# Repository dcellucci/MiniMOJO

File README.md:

# MiniMOJO

Documentation, hardware, and software related to MiniMOJO, a robot capable of traversing a digital cellular solids lattice.

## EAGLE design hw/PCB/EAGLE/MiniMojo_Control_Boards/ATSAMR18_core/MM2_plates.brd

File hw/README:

# Hardware Notes

## MOJO Boards Rev 3

That's the one with the battery backpack.

### TeuxDeux

 1. Add solder jumper to disconnect power for I2C cable
 2. Move backpack switch to somewhere reachable
 	2a. backpack switch should turn IC on/off, IC should turn motors on/off
 3. Move servo connector up

### Notes

Pinout for ATSAM

    6 Pin | 10 Pin SAM 

    1 > 2
    2 > 1
    3 > 4
    4 > DNC 
    5 > 0
    6 > 5

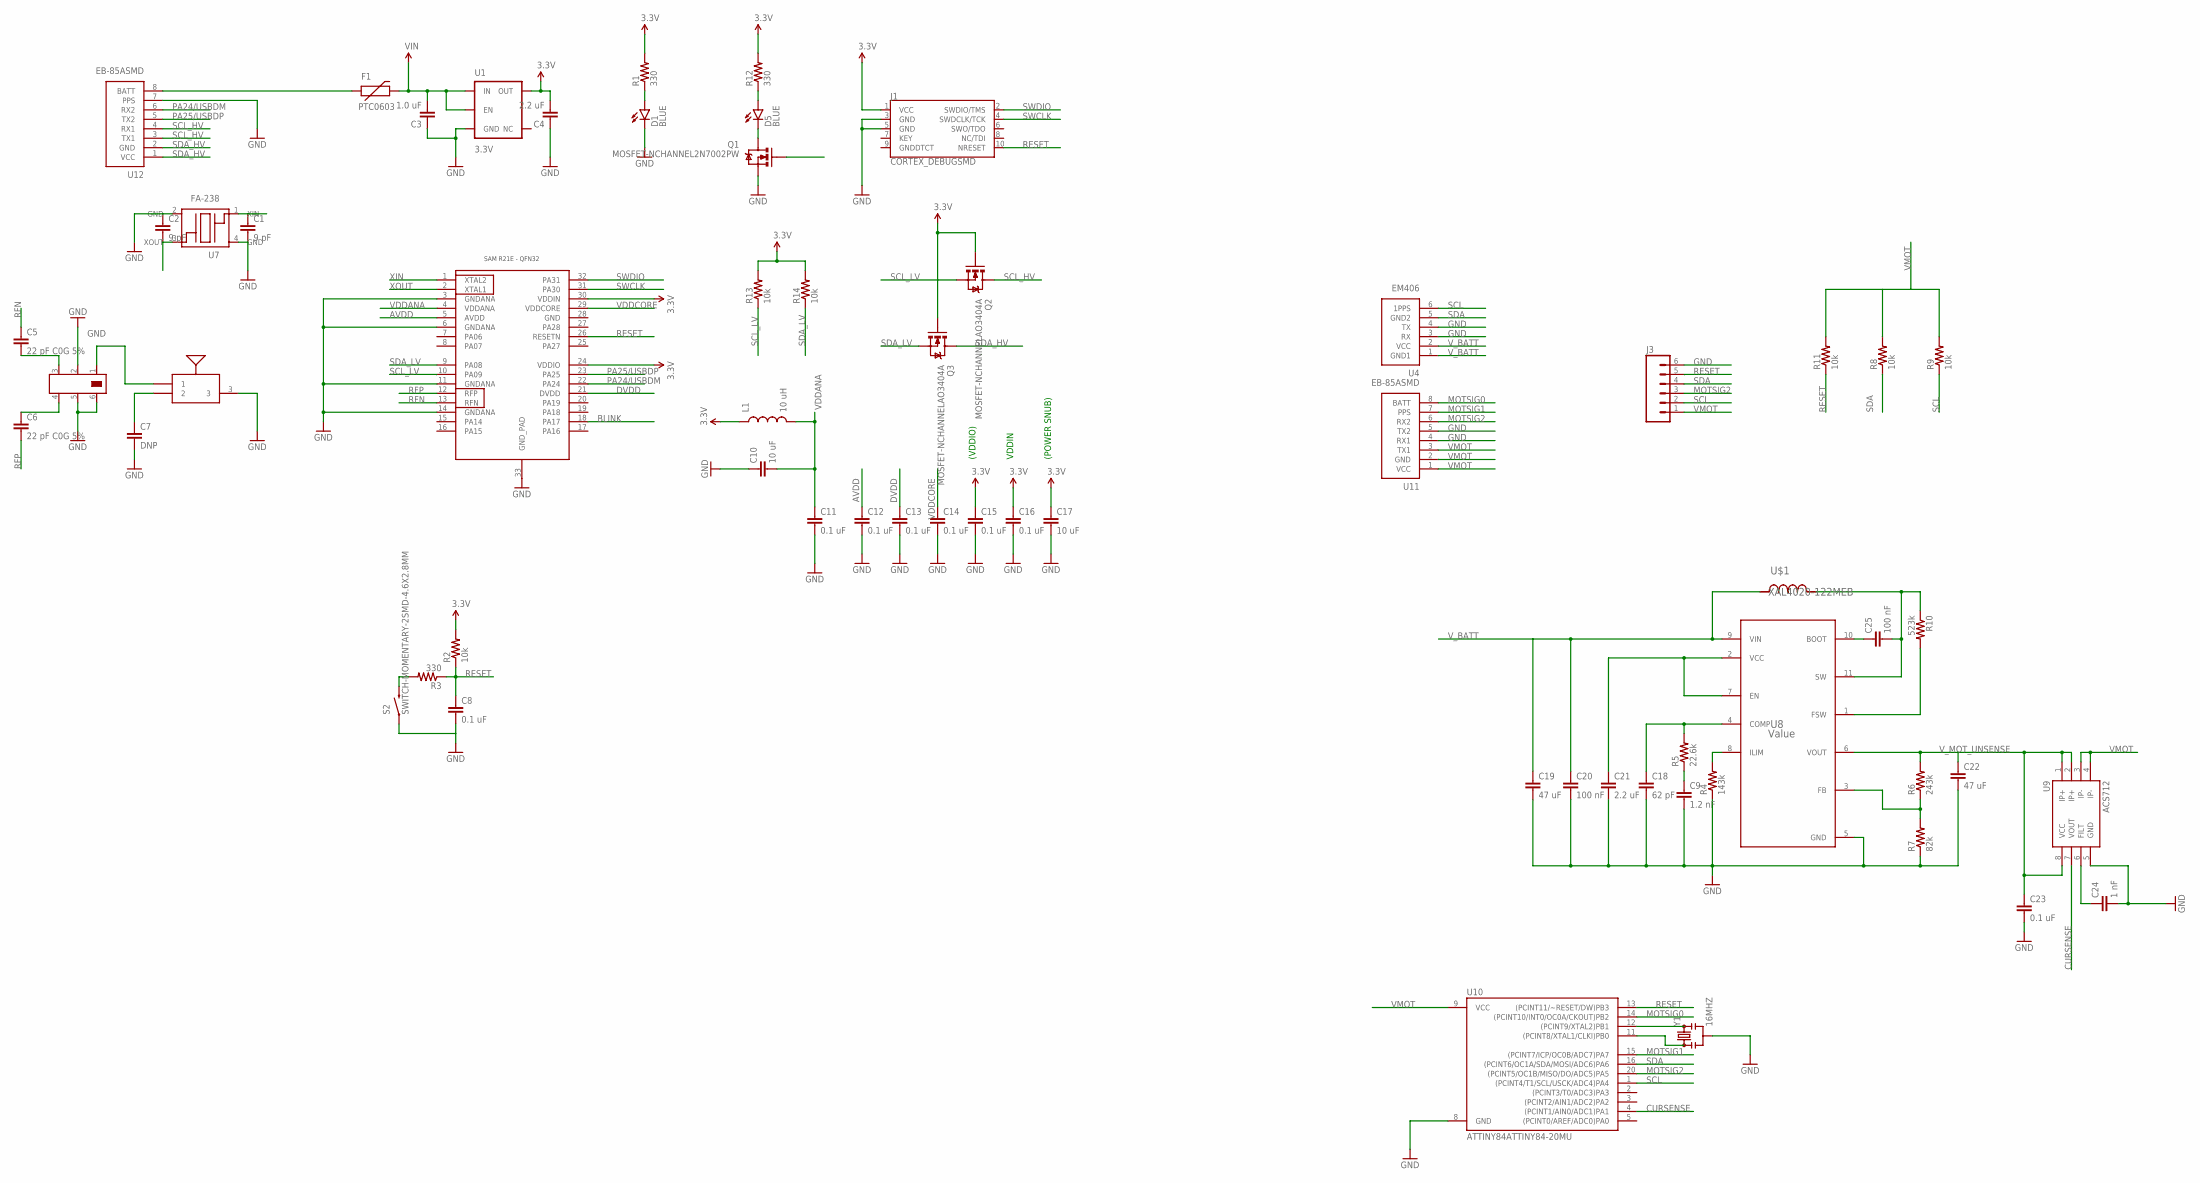
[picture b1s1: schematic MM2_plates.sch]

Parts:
C1, C2: 9 pF; 0402-CAP
C3: 1.0 uF; 0402-CAP
C4: 2.2 uF; 0402-CAP
C5, C6: 22 pF C0G 5%; 0402-CAP
C7: DNP; 0402-CAP
C8, C11, C12, C13, C14, C15, C16, C23: 0.1 uF; 0402-CAP
C9: 1.2 nF; 0805
C10, C17: 10 uF; 0402-CAP
C18: 62 pF; 0805
C19, C22: 47 uF; 1206
C20, C25: 100 nF; 0402-CAP
C21: 2.2 uF; 0603-CAP
C24: 1 nF; 0402-CAP
D1, D5: BLUE; LED-0603
F1: PTC0603; 0603
J1: CORTEX_DEBUGSMD; SAMTECH_FTSH-105-01
J3: M06SMD-1MM; 1X06-1MM
L1: 10 uH; 0603
Q1: MOSFET-NCHANNEL2N7002PW; SOT323
Q2, Q3: MOSFET-NCHANNELAO3404A; SOT23-3
R1, R3, R12: 330; 0402-RES
R2, R8, R9, R11, R13, R14: 10k; 0402-RES
R4: 143k; 1206
R5: 22.6k; 0402-RES
R6: 243k; 0402-RES
R7: 82k; 0603-RES
R10: 523k; 1206
S2: SWITCH-MOMENTARY-2SMD-4.6X2.8MM; TACTILE_SWITCH_SMD_4.6X2.8MM
U1: 3.3V; SOT23-5
U2: ATSAMR21E18A-MUT; QFN32
U4: EM406
U5: PULSE_ANT_2.4GHZ; ANT_BAR
U6: JOHANSON_2450BM15A0015E; 0805_BALUN
U7: FA-238
U8: Value; RNR0011A
U9: ACS712; SO08
U10: ATTINY84ATTINY84-20MU; QFN20
U11, U12: EB-85ASMD; EB-85A
U$1: XAL4020-122MEB; XAL4020
Y1: 16MHZ; RESONATOR-SMD

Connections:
3.3V: C4.2, C15.1, C16.1, C17.1, J1.1 (VCC), L1.1, Q2.1 (G), Q3.1 (G), R1.2, R2.2, R12.2, R13.2, R14.2, U1.5 (OUT), U2.24 (VDDIO), U2.30 (VDDIN)
AVDD: C12.1, U2.5 (AVDD)
BLINK: Q1.1 (G), U2.18 (PA17)
CURSENSE: U9.7 (VOUT), U10.4 ((PCINT1/AIN0/ADC1)PA1)
DVDD: C13.1, U2.21 (DVDD)
GND: C1.2, C2.1, C3.1, C4.1, C7.2, C8.2, C9.2, C10.1, C11.2, C12.2, C13.2, C14.2, C15.2, C16.2, C17.2, C18.2, C19.2, C20.2, C21.2, C22.2, C23.2, C24.2, D1.C, J1.3 (GND), J1.5 (GND), J3.6, Q1.2 (S), R4.1, R7.1, S2.1, S2.2 (1), U1.2 (GND), U2.3 (GNDANA), U2.6 (GNDANA), U2.11 (GNDANA), U2.14 (GNDANA), U2.33 (GND_PAD), U4.3 (RX), U4.4 (TX), U5.3, U6.2, U6.5, U6.6, U7.2 (GND), U7.4 (GND), U8.5 (GND), U9.5 (GND), U10.8 (GND), U11.4 (RX1), U11.5 (TX2), U12.7 (PPS), Y1.2
MOTSIG0: U10.14 ((PCINT10/INT0/OC0A/CKOUT)PB2), U11.8 (BATT)
MOTSIG1: U10.15 ((PCINT7/ICP/OC0B/ADC7)PA7), U11.7 (PPS)
MOTSIG2: J3.3, U10.20 ((PCINT5/OC1B/MISO/DO/ADC5)PA5), U11.6 (RX2)
unnamed: F1.1, U12.8 (BATT)
unnamed: R3.2, S2.3 (2), S2.4 (2)
unnamed: R4.2, U8.8 (ILIM)
unnamed: U10.12 ((PCINT9/XTAL2)PB1), Y1.3
unnamed: U10.11 ((PCINT8/XTAL1/CLKI)PB0), Y1.1
unnamed: U5.1, U6.1
unnamed: C7.1, U5.2
unnamed: D1.A, R1.1
unnamed: C5.2, U6.3
unnamed: C6.1, U6.4
unnamed: C9.1, R5.1
unnamed: C18.1, R5.2, U8.4 (COMP)
unnamed: C24.1, U9.6 (FILT)
unnamed: C21.1, U8.2 (VCC), U8.7 (EN)
unnamed: D5.A, R12.1
unnamed: D5.C, Q1.3 (D)
unnamed: C25.1, U8.10 (BOOT)
unnamed: C25.2, R10.1, U8.11 (SW), U$1.2
unnamed: R10.2, U8.1 (FSW)
unnamed: R6.1, R7.2, U8.3 (FB)
PA24/USBDM: U2.22 (PA24), U12.6 (RX2)
PA25/USBDP: U2.23 (PA25), U12.5 (TX2)
RESET: C8.1, J1.10 (NRESET), J3.5, R2.1, R3.1, R11.1, U2.26 (RESETN), U10.13 ((PCINT11/~RESET/DW)PB3)
RFN: C5.1, U2.13 (RFN)
RFP: C6.2, U2.12 (RFP)
SCL: J3.2, R9.1, U4.6 (1PPS), U10.1 ((PCINT4/T1/SCL/USCK/ADC4)PA4)
SCL_HV: Q2.3 (D), U12.3 (TX1), U12.4 (RX1)
SCL_LV: Q2.2 (S), R13.1, U2.10 (PA09)
SDA: J3.4, R8.1, U4.5 (GND2), U10.16 ((PCINT6/OC1A/SDA/MOSI/ADC6)PA6)
SDA_HV: Q3.3 (D), U12.1 (VCC), U12.2 (GND)
SDA_LV: Q3.2 (S), R14.1, U2.9 (PA08)
SWCLK: J1.4 (SWDCLK/TCK), U2.31 (PA30)
SWDIO: J1.2 (SWDIO/TMS), U2.32 (PA31)
VDDANA: C10.2, C11.1, L1.2, U2.4 (VDDANA)
VDDCORE: C14.1, U2.29 (VDDCORE)
VIN: C3.2, F1.2, U1.1 (IN), U1.3 (EN)
VMOT: J3.1, R8.2, R9.2, R11.2, U9.3 (IP-), U9.4 (IP-), U10.9 (VCC), U11.1 (VCC), U11.2 (GND), U11.3 (TX1)
V_BATT: C19.1, C20.1, U4.1 (GND1), U4.2 (VCC), U8.9 (VIN), U$1.1
V_MOT_UNSENSE: C22.1, C23.1, R6.2, U8.6 (VOUT), U9.1 (IP+), U9.2 (IP+), U9.8 (VCC)
XIN: C1.1, U2.1 (XTAL2), U7.1 (XIN)
XOUT: C2.2, U2.2 (XTAL1), U7.3 (XOUT)

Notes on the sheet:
(VDDIO)
VDDIN
(POWER SNUB)

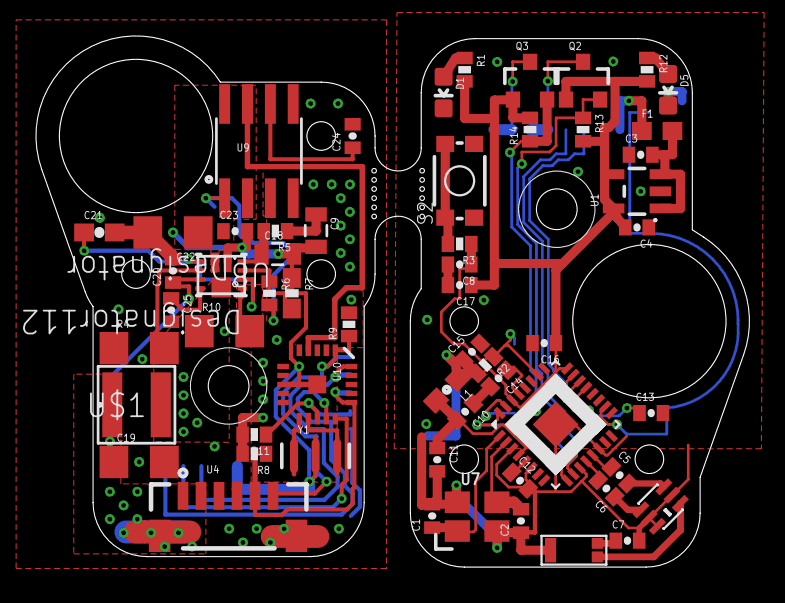
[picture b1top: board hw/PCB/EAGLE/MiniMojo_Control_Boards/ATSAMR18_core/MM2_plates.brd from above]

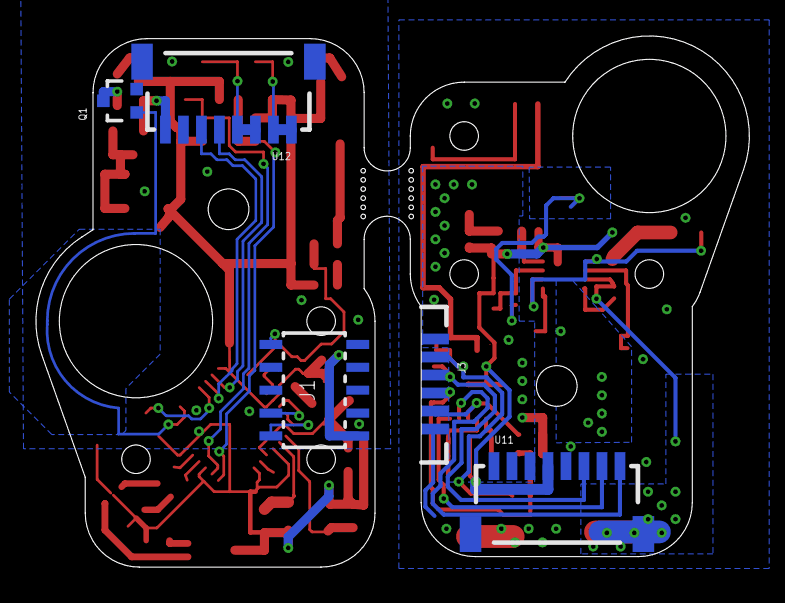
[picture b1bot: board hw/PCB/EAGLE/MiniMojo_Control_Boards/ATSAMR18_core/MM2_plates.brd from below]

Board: 2 copper layers, 39.6 x 29.5 mm, 62 parts (5 on the bottom side), 50 nets.

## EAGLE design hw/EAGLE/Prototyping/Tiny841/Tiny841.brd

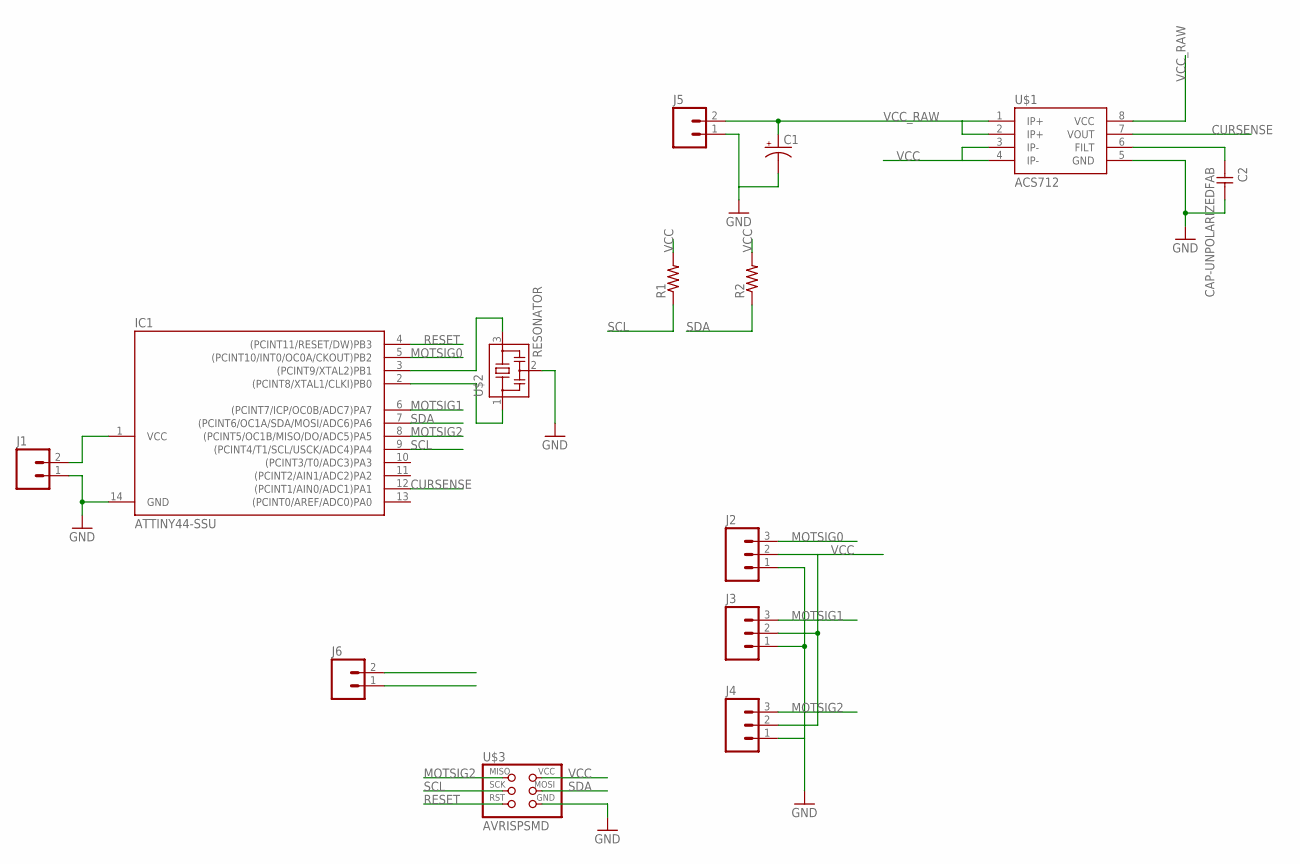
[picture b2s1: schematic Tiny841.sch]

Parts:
C1: 47UF-50V-20%(ELECT); PANASONIC_D
C2: CAP-UNPOLARIZEDFAB; C1206FAB
IC1: ATTINY44-SSU; SOIC14
J1, J6: M02PTH; 1X02
J2, J3, J4: M03PTH; 1X03
J5: M023.5MM-NO_SILK; SCREWTERMINAL-3.5MM-2-NS
R1, R2: RES-US1206FAB; R1206FAB
U$1: ACS712; SO08
U$2: RESONATOR; EFOBM
U$3: AVRISPSMD; 2X03SMD

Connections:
CURSENSE: IC1.12 ((PCINT1/AIN0/ADC1)PA1), U$1.7 (VOUT)
GND: C1.-, C2.2, IC1.14 (GND), J1.1, J2.1, J3.1, J4.1, J5.1, U$1.5 (GND), U$2.2, U$3.6 (GND)
MOTSIG0: IC1.5 ((PCINT10/INT0/OC0A/CKOUT)PB2), J2.3
MOTSIG1: IC1.6 ((PCINT7/ICP/OC0B/ADC7)PA7), J3.3
MOTSIG2: IC1.8 ((PCINT5/OC1B/MISO/DO/ADC5)PA5), J4.3, U$3.1 (MISO)
unnamed: IC1.3 ((PCINT9/XTAL2)PB1), U$2.3
unnamed: IC1.2 ((PCINT8/XTAL1/CLKI)PB0), U$2.1
unnamed: C2.1, U$1.6 (FILT)
RESET: IC1.4 ((PCINT11/RESET/DW)PB3), U$3.5 (RST)
SCL: IC1.9 ((PCINT4/T1/SCL/USCK/ADC4)PA4), J6.1, R1.1, U$3.3 (SCK)
SDA: IC1.7 ((PCINT6/OC1A/SDA/MOSI/ADC6)PA6), J6.2, R2.1, U$3.4 (MOSI)
VCC: IC1.1 (VCC), J1.2, J2.2, J3.2, J4.2, R1.2, R2.2, U$1.3 (IP-), U$1.4 (IP-), U$3.2 (VCC)
VCC_RAW: C1.+, J5.2, U$1.1 (IP+), U$1.2 (IP+), U$1.8 (VCC)

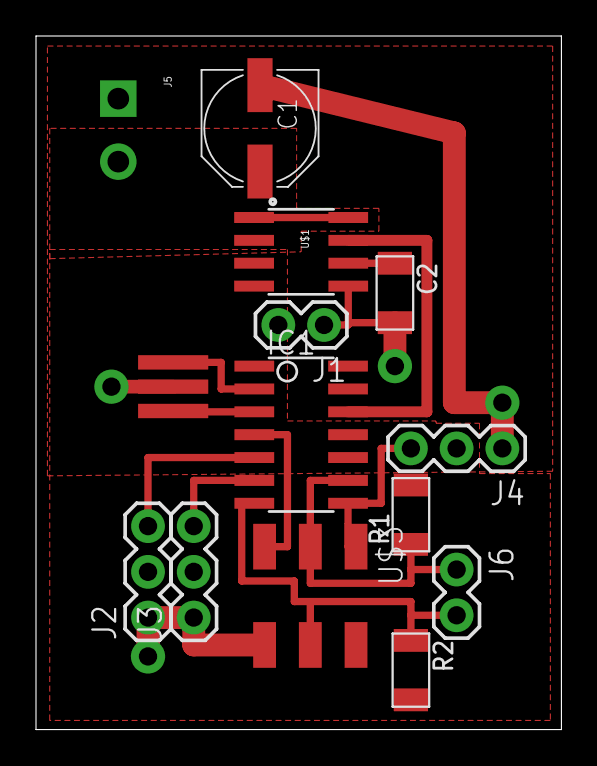
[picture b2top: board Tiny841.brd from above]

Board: 2 copper layers, 29.2 x 38.5 mm, 14 parts (0 on the bottom side), 13 nets.

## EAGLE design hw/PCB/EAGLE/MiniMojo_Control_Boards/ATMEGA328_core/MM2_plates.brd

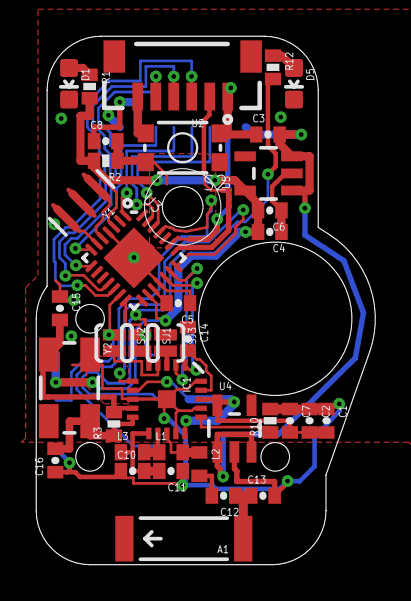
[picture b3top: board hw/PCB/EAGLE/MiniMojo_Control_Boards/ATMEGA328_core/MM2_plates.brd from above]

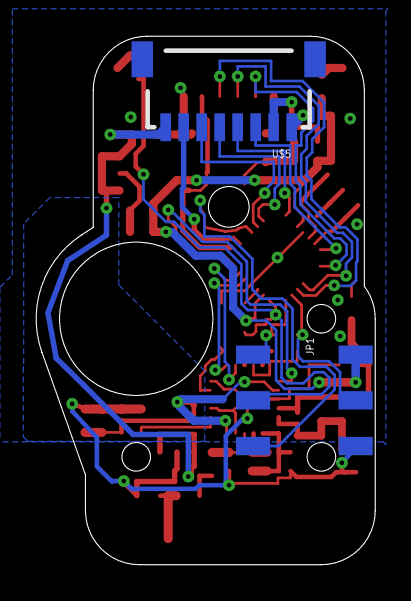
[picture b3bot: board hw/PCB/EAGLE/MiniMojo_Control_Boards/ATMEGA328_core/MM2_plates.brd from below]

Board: 2 copper layers, 18.8 x 29.4 mm, 39 parts (2 on the bottom side), 38 nets.

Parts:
A1: ANTENNA2SMD5; ANTENNA-CHIP5
C1, C3, C4: 10 uF; 0402-CAP
C2: 10 nF; 0402-CAP
C5, C6, C8: 0.1 uF; 0402-CAP
C7: 1 nF; 0402-CAP
C10: 2.2 nF; 0402-CAP
C11: 4.7 pF; 0402-CAP
C12: 1.5 pF; 0402-CAP
C13: 1.0 pF; 0402-CAP
C14: 33 nF; 0402-CAP
C15, C16: 22 pF; 0402-CAP
D1, D5: BLUE; LED-0603
IC1: NRF24L01SMD; QFN20
JP1: 2X3_SMD
L1: 8.2 nH; C0402
L2: 3.9 nH; C0402
L3: 2.7 nH; C0402
R1, R2: 10k; 0402-RES
R3: 1M; 0402-RES
R10: 22k; 0402-RES
R12: 330; 0402-RES
S2: Reset; TACTILE_SWITCH_SMD_4.6X2.8MM
SJ1, SJ2, SJ3: JUMPER-PAD-2-NOYES_SILK; PAD-JUMPER-2-NO_YES_SILK
U2: EM406
U3: ATMEGA328P_VQFNVQFN; VQFN-28
U4: 3.3V; SOT23-5
U5: 5V; SOT23-5
U$5: EB-85ASMD; EB-85A
Y1: 16MHZ; RESONATOR-SMD
Y2: 16 MHz; CRYSTAL-SMD-5X3

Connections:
3.3V: C1.2, C2.2, C7.2, IC1.7, IC1.15, IC1.18, U4.5
5V: C4.2, C6.2, JP1.2, R1.2, R2.2, U3.3, U3.16, U5.5
CE: IC1.1, U3.19
CSN: IC1.2, U3.20
CURRENT_SENSE1: U3.23, U$5.7
CURRENT_SENSE2: U2.2, U3.22
DTR: C8.1, U$5.2
GND: C1.1, C2.1, C3.1, C4.1, C5.1, C6.1, C7.1, C10.1, C11.1, C13.2, C14.1, C15.1, C16.1, D1.C, D5.C, IC1.0, IC1.8, IC1.14, IC1.17, IC1.20, JP1.6, R10.2, S2.1, S2.2, U2.1, U2.6, U3.4, U3.18, U3.PAD, U4.2, U5.2, U$5.1, Y1.2
HIP: U2.3, U3.12
IRQ: IC1.6, U3.21
MISO: JP1.1, SJ1.1, U3.14
MOSI: JP1.4, SJ2.1, U3.13
unnamed: U3.5, Y1.1
unnamed: U3.6, Y1.3
unnamed: D1.A, R1.1
unnamed: IC1.12, L1.1, L3.2
unnamed: C5.2, U3.17
unnamed: IC1.13, L1.2, L2.1
unnamed: C12.2, L2.2
unnamed: D5.A, R12.1
unnamed: A1.FEED, C12.1, C13.1
unnamed: IC1.3, SJ3.2
unnamed: C10.2, C11.2, IC1.11, L3.1
unnamed: C14.2, IC1.19
unnamed: IC1.16, R10.1
unnamed: IC1.4, SJ2.2
unnamed: C15.2, IC1.9, R3.2, Y2.1
unnamed: C16.2, IC1.10, R3.1, Y2.3
unnamed: IC1.5, SJ1.2
RESET: C8.2, JP1.5, R2.1, S2.3, S2.4, U3.25
RXI: U3.26, U$5.6
SCK: JP1.3, R12.2, SJ3.1, U3.15
SERVOB1: U2.5, U3.8
SERVOB2: U2.4, U3.11
SERVOT1: U3.1, U$5.4
SERVOT2: U3.7, U$5.3
TXO: U3.27, U$5.5
VIN: C3.2, U4.1, U4.3, U5.1, U5.3, U$5.8

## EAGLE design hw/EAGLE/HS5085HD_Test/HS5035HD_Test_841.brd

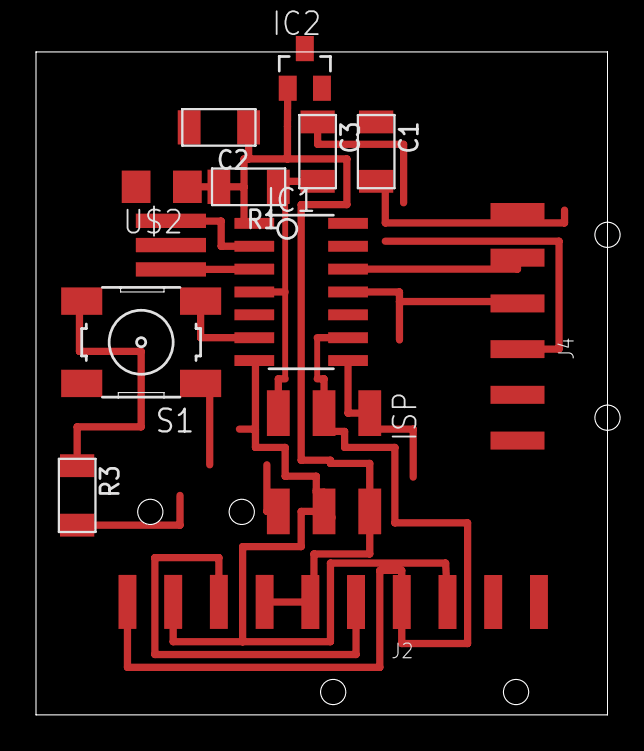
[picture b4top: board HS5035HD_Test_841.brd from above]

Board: 2 copper layers, 31.8 x 36.8 mm, 14 parts (0 on the bottom side), 13 nets.

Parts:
C1, C2, C3: 10 uF; C1206FAB
IC1: ATTINY44-SSU; SOIC14
IC2: SOT23
ISP: AVRISPSMD; 2X03SMD
J1: TMP007; 1X04-SMD
J2: INA219; 1X06-SMD
J4: RA 6Pin SMD; 1X06-SMD
R1, R3: R1206FAB
S1: 6MM_SWITCH
U$1: RESONATOR; EFOBM
U$2: LED; LED1206

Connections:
GND: C1.2, C2.2, IC1.14, IC2.3, ISP.6, J1.2, J2.2, J4.1, J4.2, S1.1, S1.2, U$1.2, U$2.2
MISO: IC1.8, ISP.1
MOSI: IC1.7, ISP.4, J1.3, J2.4
unnamed: IC1.3, U$1.3
unnamed: IC1.2, U$1.1
unnamed: C3.1, J4.6
RAW: C1.1, IC2.2, J2.6
RST: C3.2, IC1.4, ISP.5, R1.1
RXI: IC1.11, J4.4
SCK: IC1.9, ISP.3, J1.4, J2.3
SW: IC1.6, R3.1, S1.3, S1.4
TXO: IC1.12, J4.5
VCC: C2.1, IC1.1, IC2.1, ISP.2, J1.1, J2.1, J4.3, R1.2, R3.2, U$2.1

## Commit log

2016-08-25 Added Gear Generation notes
2016-08-26 Added CAD files of MOJO
2016-08-29 updated CAD, added Eagle Boards (ATSAM and ATMEGA)
2016-08-29 Added TPS61089 library
2016-08-30 Made TPS61089 mods
2016-09-02 added TPS61089 w/ Tiny841
2016-09-02 Added finished 841 schematic
2016-09-03 Added new MM arms
2016-09-03 added full 841 board
2016-09-07 added new arms, control code
2016-09-08 making changes
2016-09-23 too long since commiting...
2016-09-23 removed 3dm's (because they're huge)
2016-09-23 removed more 3dms
2016-09-23 added descriptive sw tutorial (start)
2016-09-23 smaller images
2016-09-23 changed image size 2
2016-09-24 Added spline pattern
2016-09-24 updated hub drawing
2016-11-15 post 0g
2016-11-15 Adding CC (computer control) code
2016-11-15 Added readme for computer controller
2016-11-15 improved readme for computer controller
2016-11-15 Added current reading output parsing
2016-11-15 cleaning
2016-11-16 ascii art
2016-11-16 Changed servo order to appease people
2016-11-20 Test Stand models
2016-11-21 Added Fab Modules UI
2016-11-30 Added custom modules
2017-02-09 Rev 3 MM boards and Migration to KICAD
2017-02-09 Added annotated platecad
2017-02-10 ATSAMD11_Core layout using KiCAD
2017-02-11 Added hex spacer, reorganized CAD modules
2017-02-11 Added board stack spacer
2017-02-13 Added ATSAMD11 AAtmel smart code
2017-02-16 Added stp files for updated MM components
2017-02-22 long time since commit
2017-02-22 new lib INA3221
2017-02-23 added include wire statement
2017-02-23 INA3221 refactor to class and format like dps310
2017-02-23 Added serial javascript files
2017-02-23 moved INA3221 to CSL-Part-Library
2017-02-27 Lots of changes- firmware, board rev, mods
2017-02-28 Added addendum to boards, modules for debug, comms description
2017-02-28 V1 Comms Spec
2017-02-28 more comms edits
2017-02-28 fixing github problems
2017-02-28 github debug
2017-02-28 line spacing...?
2017-02-28 that didn't work
2017-02-28 finally?
2017-03-02 Latency Test, firmware development
2017-03-02 working ingest of mojo json
2017-03-03 more firmware, a working websocket serial node
2017-03-03 cleanedup getMojoJsonData.js
2017-03-06 Added IK input information
2017-03-15 fixed connection; wasn't passing comm port to serial open()
2017-03-15 working WINDOWS websocket; tmp fix on malformed json possibly from irregular event call
2017-03-15 added DISPLAY2.js
2017-03-17 added working data_logger.js
2017-03-17 updated websocket for windows; working power mon and data logger
2017-03-18 working mojo plotting = MOJO_canvas_plotter
2017-03-20 ...I forgot to commit for a while
2017-03-20 Added firmware def
2017-03-20 added motor positions
2017-03-20 added servomotor value descriptions
2017-04-04 Adding latency tests + serial work
2017-04-06 Added mojo scheduler
2017-04-11 translated results from 0g test (day 2)

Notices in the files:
parts and their libraries:
SparkFun-Connectors: Licensing: Creative Commons ShareAlike 4.0 International - https://creativecommons.org/licenses/by-sa/4.0
